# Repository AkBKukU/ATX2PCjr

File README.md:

# ATX to PCjr

An ATX to IBM PCjr adapter board

This allows you to use a standard ATX power supply to power an IBM PC jr.

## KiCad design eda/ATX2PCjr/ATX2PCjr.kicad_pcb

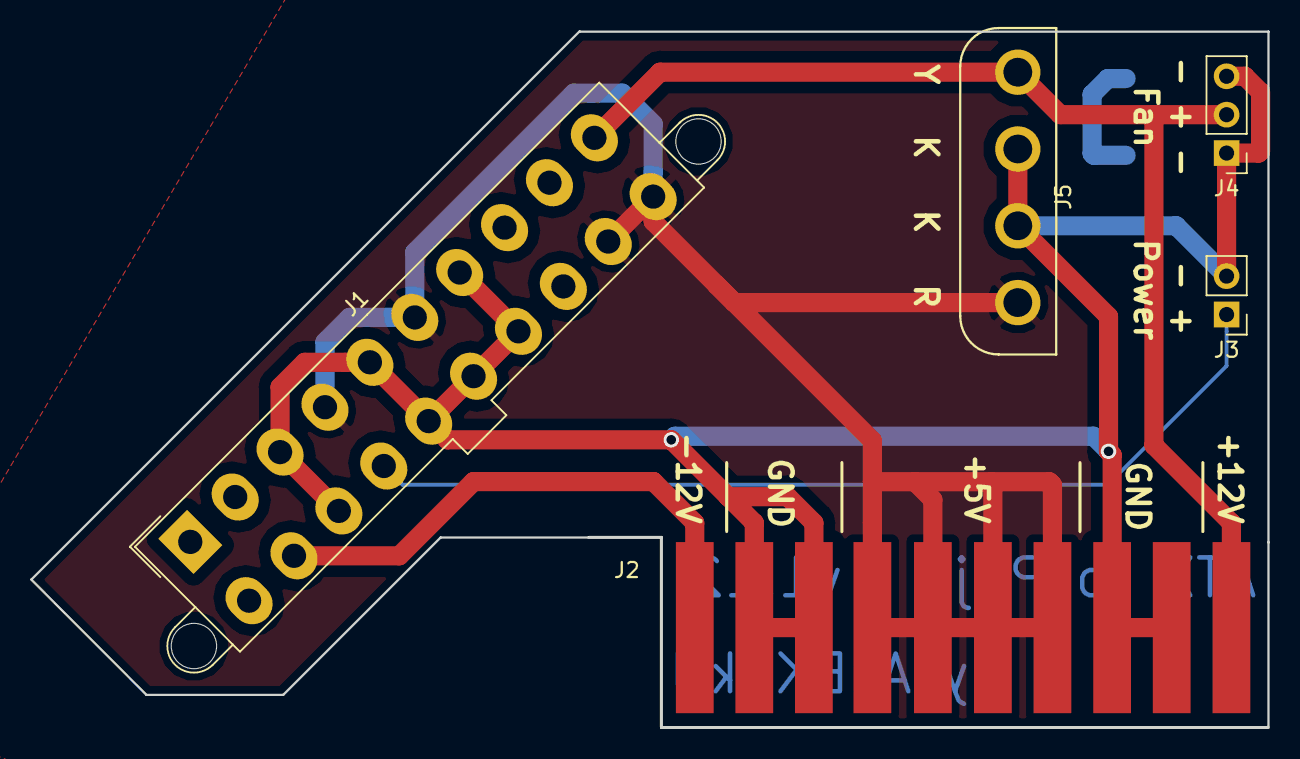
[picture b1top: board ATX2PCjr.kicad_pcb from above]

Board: 2 copper layers, 81.8 x 46.0 mm, 5 parts (0 on the bottom side), 5 nets.

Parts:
J1: ATX Connector; Molex_Mini-Fit_Jr_5566-20A2_2x10_P4.20mm_Vertical-LARGE
J2: PCjr Card Edge; PCjr Power Board Card Edge
J3: Power Switch Header; PinHeader_1x02_P2.54mm_Vertical
J4: Fan Header; PinHeader_1x03_P2.54mm_Vertical
J5: Floppy Power; Mate-N-Lok Vertical

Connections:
/+5V: J1.4, J1.6, J1.19, J1.20, J2.4, J2.5, J2.6, J2.7, J5.1
/+12V: J1.10, J2.10, J4.2, J5.4
/-12V: J1.12, J2.1
/GND: J1.3, J1.5, J1.7, J1.13, J1.15, J1.16, J1.17, J2.2, J2.3, J2.8, J2.9, J3.2, J4.1, J4.3, J5.2, J5.3
/PS-ON: J1.14, J3.1

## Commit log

2018-07-29 v1.0
2018-08-11 Restructure and start panel
2018-08-12 Switch to 3d printed panel
2018-08-12 Board version 1.1
2018-08-17 Update rear panel with bevel and slot option
2018-08-30 top switch
2018-09-06 update panel(s)
2018-09-06 Updated to v1.11 to fix minor issues
2018-09-06 Update image
2018-11-10 MiniFit Jr Vias and Panel Holes
2019-08-16 Switch change and reset
2019-08-20 hole size fitment
2019-08-21 Size tweak
2019-08-22 Notes printout
